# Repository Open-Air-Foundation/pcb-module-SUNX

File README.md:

# AirGradient SUNX CO₂ Sensor Module — Hardware

> KiCad hardware design files for the AirGradient SUNX CO₂ sensor module — a plug-in adapter board that carries a SenseAir Sunrise/Sunlight ("SUNX") NDIR CO₂ sensor in AirGradient air quality monitors, including the [Open Air Max](https://www.airgradient.com/professional/products/open-air-max/).

## Overview

A 2-layer adapter for the SenseAir Sunrise/Sunlight family: two sockets matching the sensor's 5-pin and 4-pin headers, an HT7333 3.3 V LDO with bulk decoupling for the sensor supply, and a solder jumper (JP1) for sensor power selection. Power and UART are routed to an 8-pin host connector.

This is the SUNX-only variant of AirGradient's CO₂ sensor adapter family — v2.0 of the original combined design with S8 support removed; the [S8-only board](https://github.com/Open-Air-Foundation/pcb-module-s8) and the [combined S8 + SUNX board](https://github.com/Open-Air-Foundation/pcb-module-s8-sunx) live in their own repositories.

## Design structure

A single KiCad project in `sunx/`: one schematic sheet and a 2-layer board.

## Repository structure

```
sunx/                        # KiCad project (schematic + board), production/
```

## Key components

| Function | Part | Ref |
|---|---|---|
| Sensor sockets (5-pin + 4-pin) | Pin sockets, 2.54 mm | J1, J2 |
| 3.3 V LDO (sensor supply) | HT7333-3 (SOT-89) | U1 |
| Bulk decoupling | 2× 10 µF, 2× 22 µF | C1–C4 |
| Sensor power select (3-way solder jumper) | — | JP1 |
| Host connector (8-pin) | Molex | con1 |

## Toolchain

- **KiCad 9** (file format 2025-01). All symbols, footprints, and 3D models come from the KiCad standard libraries — the project opens without any extra library setup.

## Fabrication

`sunx/production/` holds the released set: Gerber zip (`sunx-v2.0.zip`; the Gerber filenames inside keep the design's original `CO2-sensor-pcb` naming), BOM, and pick-and-place positions.

## Versioning & releases

Hardware revisions are tagged on this repository. Per-version release notes and the matching production file set are published on the [GitHub Releases](../../releases) page.

> The `v2.1` branch carries work in progress (AP2112K-3.3 LDO, 0 Ω power-select links replacing the solder jumper, revised silkscreen and placement). It is untested and unreleased — do not order from it.

## License

This is open-source hardware. The design files in this repository are licensed under the
[Creative Commons Attribution-ShareAlike 4.0 International (CC BY-SA 4.0)](https://creativecommons.org/licenses/by-sa/4.0/) license — see [LICENSE](LICENSE).

You are free to use, modify, and manufacture these designs, including commercially, provided you credit AirGradient and share derivative designs under the same license.

## Maintainers

AirGradient hardware team.

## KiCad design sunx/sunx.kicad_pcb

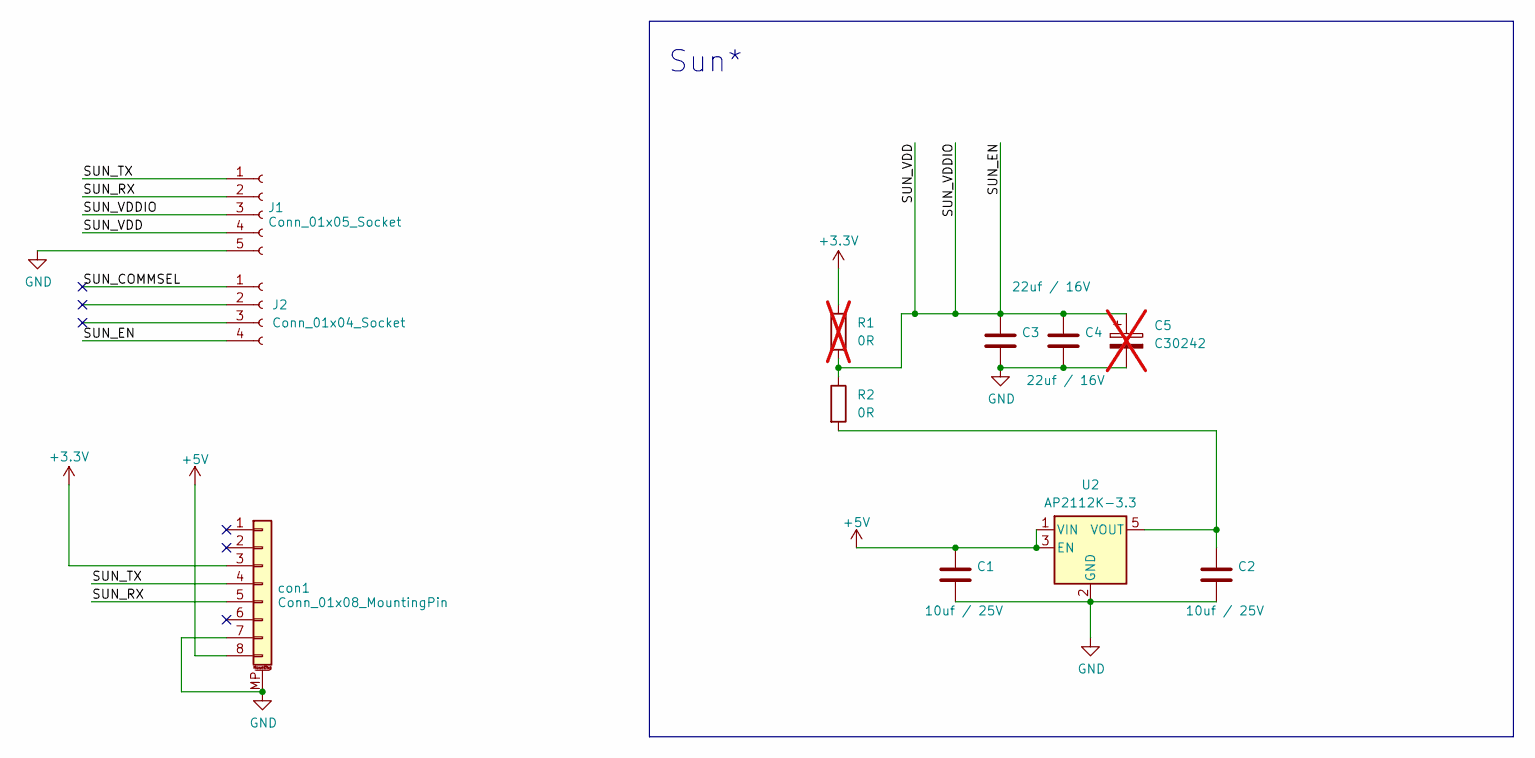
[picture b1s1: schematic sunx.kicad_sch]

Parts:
C1, C2: 10uf / 25V; C_0603_1608Metric
C3, C4: 22uf / 16V; C_0603_1608Metric
C5: C30242; CP_EIA-3528-21_Kemet-B; not fitted
J1: Conn_01x05_Socket; PinHeader_1x05_P2.54mm_Vertical
J2: Conn_01x04_Socket; PinHeader_1x04_P2.54mm_Vertical
R1: 0R; R_0603_1608Metric; not fitted
R2: 0R; R_0603_1608Metric
U2: AP2112K-3.3; SOT-23-5
con1: Conn_01x08_MountingPin; Molex_PicoBlade_53261-0871_1x08-1MP_P1.25mm_Horizontal

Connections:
+3.3V: R1.1, con1.3
+5V: C1.1, U2.1 (VIN), U2.3 (EN), con1.8
/SUN_COMMSEL: J2.1
/SUN_EN: C3.1, C4.1, C5.1, J1.3, J1.4, J2.4, R1.2, R2.1
/SUN_RX: J1.2, con1.5
/SUN_TX: J1.1, con1.4
GND: C1.2, C2.2, C3.2, C4.2, C5.2, J1.5, U2.2 (GND), con1.7, con1.MP (MountPin)
unnamed: C2.1, R2.2, U2.5 (VOUT)

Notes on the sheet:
Sun*

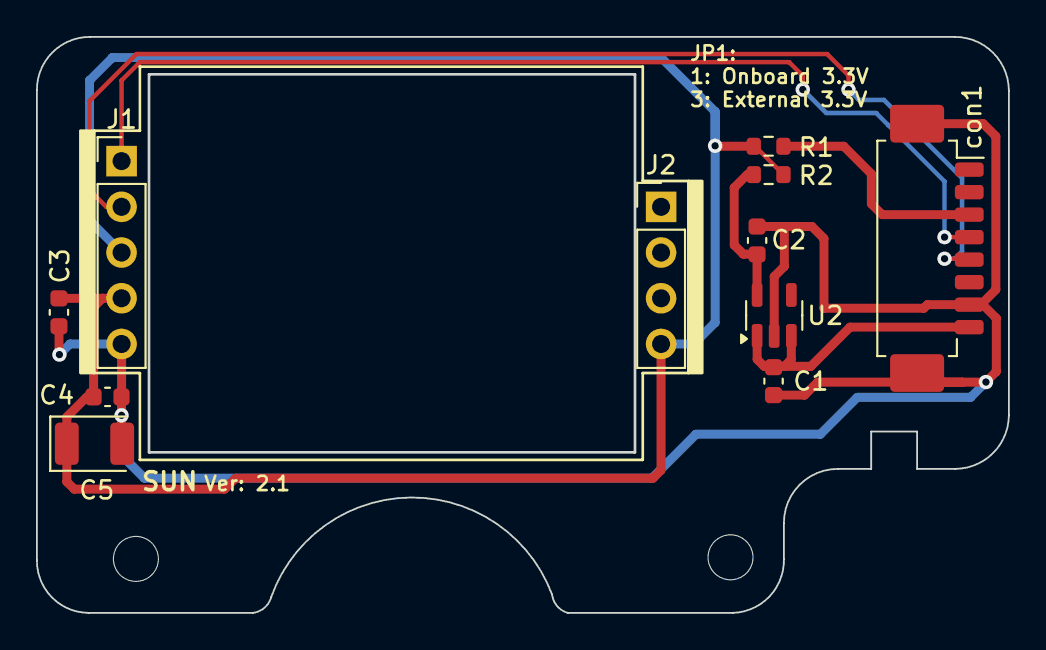
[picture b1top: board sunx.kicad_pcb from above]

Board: 2 copper layers, 54.0 x 32.0 mm, 11 parts (0 on the bottom side), 7 nets.
